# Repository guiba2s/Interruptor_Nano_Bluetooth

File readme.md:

# Interruptor Bluetooth Versão 1.0

  O interruptor Bluetooth V1.0 é uma placa que controla cargas AC por meio de dispositivos que possuem conectividade por bluetooth, como um celular por exemplo. Esse módulo é controlado por uma placa **Arduino Nano**, que é interfaceada por um módulo bluetooth, o **HC-06**, o que permite ligar e desligar cargass AC que operem nas faixas de tensão de 110V-220V com uso de um celular ios ou android.
  Projetada para caber em uma caixa de luz plástica de dimensões 4x2. Essas caixas são bastante
comuns nas maiorias das residências do país, o que torna desnecessário quebrar paredes para a instalação
da placa.
  Possui **_custo relativamente baixo_** e a simplicidade de sua instalação torna o projeto economicamente viável.
Para sua instalação, apenas conhecimentos básicos sobre elétrica se fazem necessários.

# Caracteristicas:
* Controlado por Arduino Nano; 
* Alimentação: 110V ~ 220V;
* Módulo Bluetooth: HC-06;
* Dimensões: 65mm x 45mm;
* Fonte Hi-Link: Input 110V~220V. Output:5V;
* Led indicativo de acionamento do relé;
* Relé de estado sólido;

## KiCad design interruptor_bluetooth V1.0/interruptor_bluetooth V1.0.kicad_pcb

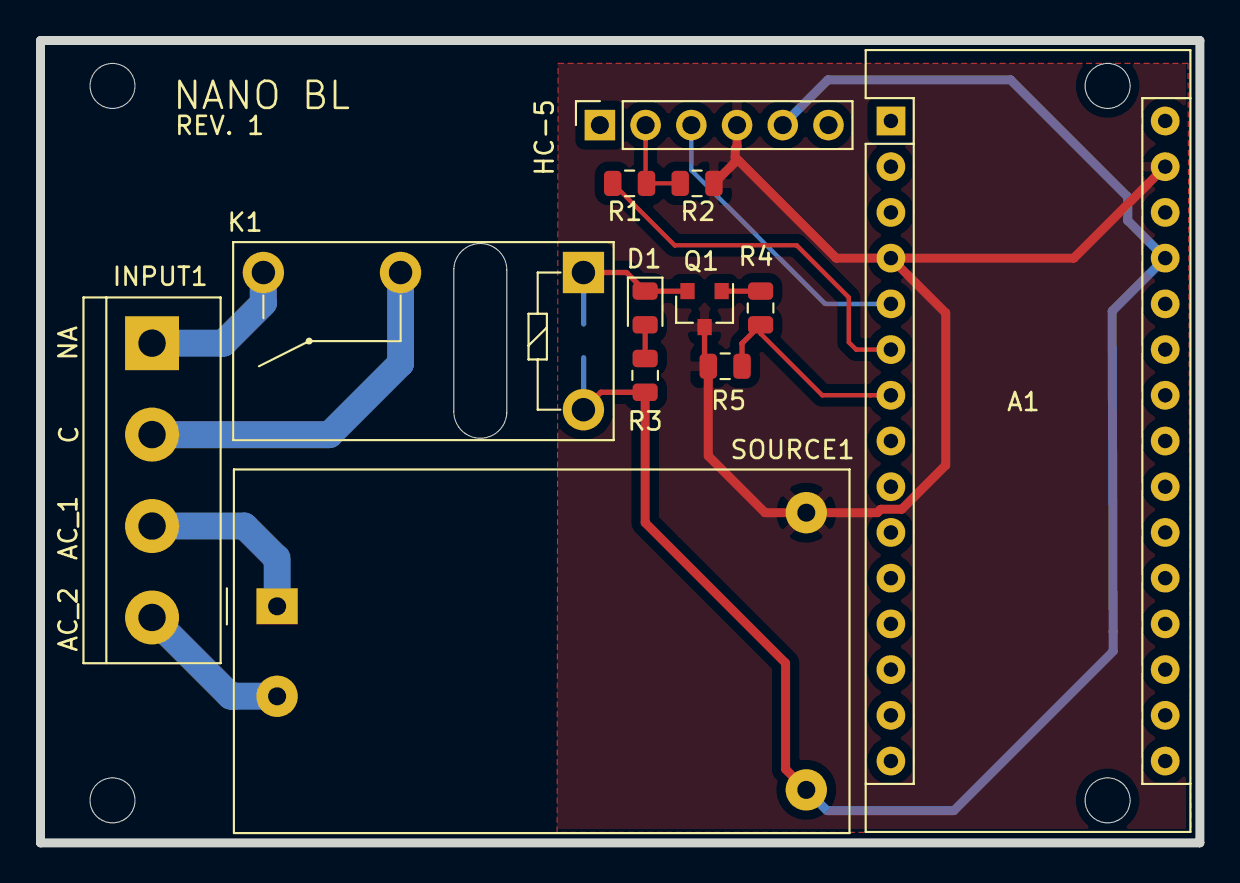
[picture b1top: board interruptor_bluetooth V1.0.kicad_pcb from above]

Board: 2 copper layers, 64.4 x 44.6 mm, 17 parts (1 on the bottom side), 13 nets.

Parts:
A1: Arduino_Nano_v3.x; Arduino_Nano
D1: LED; LED_0805_2012Metric
D2: DIODE; D_0805_2012Metric
HC-5: MODULE; PinSocket_1x06_P2.54mm_Vertical
INPUT1: Conn_01x04; TerminalBlock_bornier-4_P5.08mm
K1: G5Q-1A; Relay_SPST_Omron-G5Q-1A
P3, P4, P5, P6: CONN_01X01; MountingHole_2.5mm
Q1: Q_NPN_BCE; SOT-23
R1: 1k; R_0805_2012Metric
R2: 2k; R_0805_2012Metric
R3, R4: 330R; R_0805_2012Metric
R5: 10K; R_0805_2012Metric
SOURCE1: HLK-PM01; Converter_ACDC_HiLink_HLK-PMxx

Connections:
+5V: A1.27, D2.2, HC-5.5, K1.5, R3.2, SOURCE1.4
/AC_1: INPUT1.3, SOURCE1.1
/AC_2: INPUT1.4, SOURCE1.2
/C: INPUT1.2, K1.2
/NA: INPUT1.1, K1.3
/RELE_pin: A1.7, R4.2, R5.2
/RX: A1.6, R1.2
/RX_M: HC-5.2, R1.1, R2.2
/TX: A1.5, HC-5.3
GND: A1.4, A1.29, HC-5.4, Q1.3, R2.1, R5.1, SOURCE1.3
unnamed: D1.1, D2.1, K1.1, Q1.2
unnamed: D1.2, R3.1
unnamed: Q1.1, R4.1

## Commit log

2020-11-11 upload das pastas
2020-11-11 Update readme.md
    upload da foto para readme
